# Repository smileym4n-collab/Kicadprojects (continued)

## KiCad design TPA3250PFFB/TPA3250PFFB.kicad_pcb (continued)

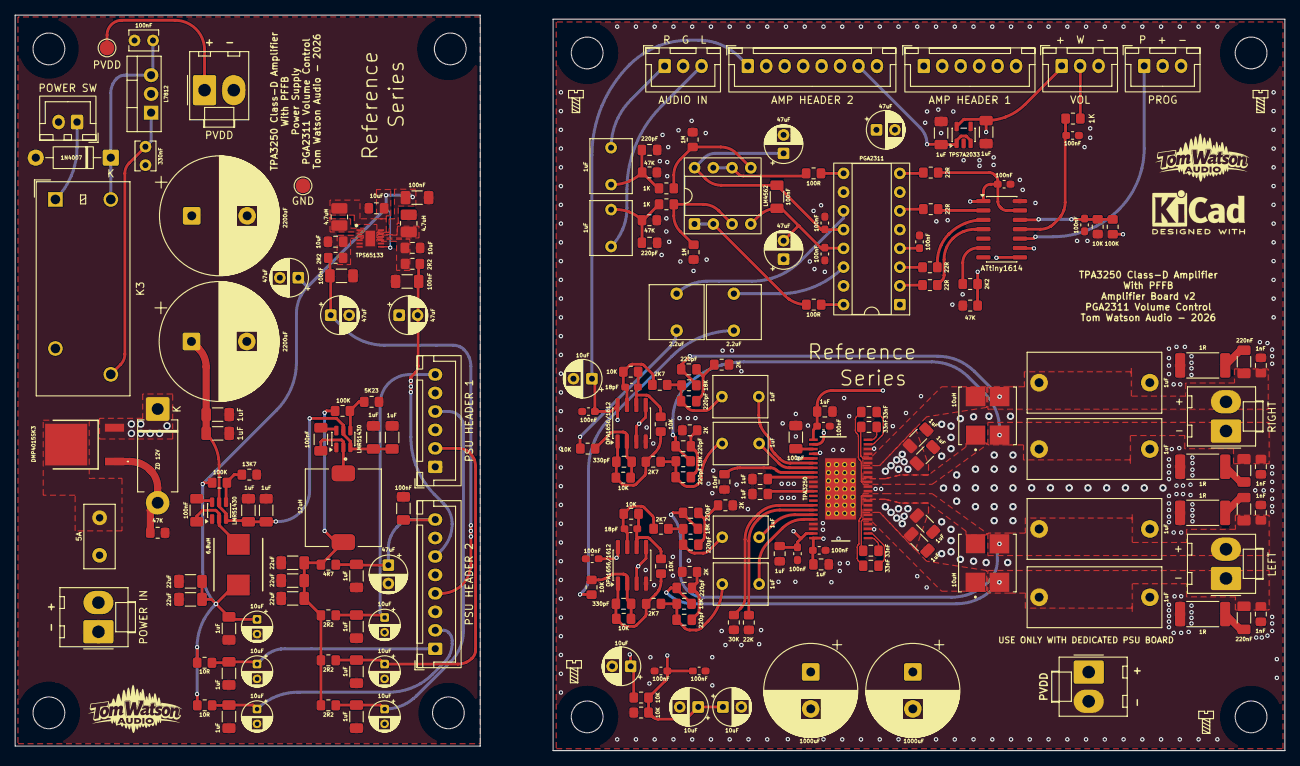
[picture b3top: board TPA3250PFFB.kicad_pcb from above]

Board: 4 copper layers, 172.0 x 99.6 mm, 218 parts (0 on the bottom side), 111 nets.

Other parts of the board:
J17: LEFT; Molex_KK-396_A-41791-0002_1x02_P3.96mm_Vertical
J18: RIGHT; Molex_KK-396_A-41791-0002_1x02_P3.96mm_Vertical

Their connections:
unnamed 66: J17.1; also elsewhere on the board
unnamed 67: J17.2; also elsewhere on the board
unnamed 68: J18.1; also elsewhere on the board
unnamed 69: J18.2; also elsewhere on the board

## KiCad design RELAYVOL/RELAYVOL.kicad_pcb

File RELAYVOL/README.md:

# RELAYVOL

Open [RELAYVOL.kicad_pro](RELAYVOL.kicad_pro) in KiCad 10 and open its schematic. Keep [RELAYVOL.kicad_sym](RELAYVOL.kicad_sym) and [sym-lib-table](sym-lib-table) beside the project. The project-local symbol divides each physical G6K relay into a left contact, a right contact and a coil. All three units share one footprint and reference designator.

The schematic is for a 5 V proof-of-concept attenuator. The 128 settled relay states were calculated and the schematic passed ERC and a pin-by-pin netlist audit. Hardware verification is pending.

- [Bill of materials](BOM.md)
- [Purchasing and stock](PURCHASING.md)
- [Resistor calculations, 128-state truth table and loading results](ATTENUATION.md)
- [KiCad 10.0.5 ERC report](ERC.rpt)

## Passive audio path

K1 to K7 switch 0.5, 1, 2, 4, 8, 16 and 32 dB pads, respectively. Each pole's COM is the stage output. With the coil off, COM touches NC and connects the shunt resistor from output to GNDA. The signal then passes through the series resistor. With the coil on, COM touches NO, connecting the stage input straight to the stage output and disconnecting the shunt. The same mechanism switches both channels. The only common audio connection is the return.

For a target loss A in dB, the voltage ratio is `k = 10^(−A/20)`. With downstream load Z = 10 kΩ, the ideal values are `Rseries = Z × (1 − k)` and `Rshunt = Z × k / (1 − k)`. These make each inserted stage look like 10 kΩ to the preceding stage. The fitted E96 pairs use one 0.1% thin-film resistor per position. The rounded values change the nominal step sizes.

For bench use, fit R29 and R30 as 10 kΩ and use a high-impedance instrument. For a known amplifier input resistance Ramp above 10 kΩ, choose a single resistor per channel using `Rterm = 1 / (1 / 10000 − 1 / Ramp)`, with resistances in ohms. With 47 kΩ inputs the exact value is 12.7027 kΩ. Use 12.7 kΩ, 0.1%, which gives an effective 9.9983 kΩ load. A 10 kΩ amplifier already provides the termination. An amplifier below 10 kΩ cannot reach a 10 kΩ effective load by adding a parallel resistor. Include any measuring instrument that remains connected in parallel when calculating the load.

Use a low-impedance, DC-free or AC-coupled source. At 2 Vrms into approximately 10 kΩ, total resistive dissipation is about 0.4 mW per channel. The 0.125 W thin-film parts have ample power margin. The highest calculated output resistance is about 3.30 kΩ at the bench load, so source impedance and cable or amplifier capacitance should be included when measuring frequency response. Omron's low-level contact reference condition is 10 µA at 10 mV DC. Some contacts can see less current at low signal levels and high attenuation. Check low-level continuity, noise, switching artefacts and channel separation on the prototype. [Omron G6K datasheet](https://components.omron.com/us-en/system/files/2026-05/datasheet_pdf/K106-E1.pdf)

## Assembly options and connectors

| Reference | Pin 1 | Pin 2 | Pin 3 |
|---|---|---|---|
| J1 power | Regulated +5 V | GND | — |
| J2 volume pot | +5 V, clockwise end | Wiper | GND, anticlockwise end |
| J3 UPDI | UPDI data | Target +5 V sense | GND |
| J4 left input | Left signal | GNDA | — |
| J5 right input | Right signal | GNDA | — |
| J6 left output | Left signal | GNDA | — |
| J7 right output | Right signal | GNDA | — |

| Build | Fit | JP1 and JP2 | Output at reset |
|---|---|---|---|
| Initial prototype | K1–K7 and their drivers | Bridge both | Ladder at maximum attenuation |
| With mute | K1–K8 and all drivers, including Q8, D8, R45 and R46 | Leave both open | J6/J7 signal pins grounded by K8 |

With K8 fitted, low on MUTE_CTRL grounds the outputs and high passes the ladder signal. R29/R30 are on the ladder side of K8, so grounding the outputs leaves the ladders terminated. The amplifier's parallel load joins them when K8 passes audio. If the jumpers are bridged with K8 fitted, K8 can ground the ladder outputs directly. Use one assembly option per board.

## MCU and volume input

U1 uses the user-approved wide SOIC-20 footprint, 7.5 × 12.8 mm nominal body and 1.27 mm lead pitch. Verify the physical package against the footprint before assembly. The stock record identified as SSOP-20 remains a separate package question. The following map uses the documented leaded ATtiny1616 pinout. [Microchip ATtiny1616 datasheet and package drawings](https://ww1.microchip.com/downloads/en/DeviceDoc/ATtiny1614-16-17-DataSheet-DS40002204A.pdf)

| Pin | Port | Function |
|---:|---|---|
| 1 | VDD | +5 V, C4 and C5 at the MCU |
| 2 | PA4 | RELAY_0_5DB, K1 |
| 3 | PA5 | RELAY_1DB, K2 |
| 4 | PA6 | RELAY_2DB, K3 |
| 5 | PA7 | RELAY_4DB, K4 |
| 6, 7 | PB5, PB4 | Unused |
| 8 | PB3 | MUTE_CTRL, optional K8 |
| 9 | PB2 | RELAY_32DB, K7 |
| 10 | PB1 | RELAY_16DB, K6 |
| 11 | PB0 | RELAY_8DB, K5 |
| 12–15 | PC0–PC3 | Unused |
| 16 | PA0/UPDI | J3 pin 1 |
| 17 | PA1/ADC0 AIN1 | VOL_ADC |
| 18, 19 | PA2, PA3 | Unused |
| 20 | GND | Digital return |

Use the internal oscillator and retain PA0 in UPDI mode. Use target-voltage sense on J3 pin 2 with the board powered from J1. R47 and C3 give a time constant of roughly 0.10–0.35 ms, including the wiper source resistance of a 10 kΩ pot. R48 pulls VOL_ADC low if the pot is disconnected. The ADC input is intended for the short internal wiring of a passive pot powered from J2. R47 limits transient injection and C3 filters the input. The header is a 0–5 V interface.

Use ADC0 with VDD as reference so slow supply changes track the pot voltage. Average ADC readings, add hysteresis around the 127 thresholds, and qualify state changes to limit chatter. The desired attenuation index is 127 at the anticlockwise end and 0 at the clockwise end. Gate pulldowns hold the relays off while the MCU pins are inputs. Initialise output latches low before enabling output direction. With K8 fitted, keep it off through startup and attenuation changes. Measure pickup, release and bounce with the flyback diodes fitted before setting the mute timing. Binary carries can change several contacts on one adjacent volume step.

## Coil supply and grounding

J1 takes regulated 5.0 V DC. Allow 0.5 A or more at the source and check the voltage at TP1 under an all-on relay load. The coil rating is 237 Ω and 21.1 mA typical at 23 °C. Seven coils draw approximately 148 mA and eight approximately 169 mA. At 5.25 V and −10% coil resistance, eight coils alone draw about 197 mA. The standard relay's must-operate limit is 4.0 V at 23 °C. C1 provides 220 µF bulk. C2 bypasses the incoming rail, C6 bypasses the local relay rail and C4/C5 decouple U1. [Omron G6K datasheet](https://components.omron.com/us-en/system/files/2026-05/datasheet_pdf/K106-E1.pdf)

Each 2N7002K is a low-side switch with a 330 Ω gate resistor and 100 kΩ gate pulldown. SOT-23 pins 1/2/3 are gate/source/drain. The stocked Multicomp Pro part is rated for 60 V VDS, ±20 V VGS and 300 mA continuous at 25 °C. Its published on-resistance table specifies 10 V drive. Its lower-gate-voltage data are typical, so verify pull-in and drain drop at 4.75 V supply and with warmed coils. For a same-pinout procurement option, Diodes Inc. specifies a maximum of 3 Ω at 4.5 V gate drive, equivalent to about 63 mV and 1.3 mW at 21.1 mA using that limit. D1–D8 use SOD-123 pin 1 cathode to +5 V and pin 2 anode to drain. Initial flyback current is approximately the preceding coil current. [Stock MOSFET datasheet](https://www.farnell.com/datasheets/4495380.pdf) · [Diodes Inc. 2N7002K](https://www.diodes.com/assets/datasheets/ds30896.pdf) · [1N4148W SOD-123 datasheet](https://www.vishay.com/docs/86356/1n4148w.pdf)

For layout, return the drivers and supply bypass currents to J1 ground without sharing their route with audio return currents. Join GNDA to GND at NT1 near the supply return. Check any additional connection between these returns through the enclosure, source, amplifier or programmer. TP1 and TP2 expose +5 V and GND.

## Pin and footprint verification

| Part | Verified assignment |
|---|---|
| K1–K8 | Pin 1 coil positive, 8 coil negative. Left COM/NC/NO 3/2/4. Right COM/NC/NO 6/7/5. Standard G6K-2P hole pattern has 5.08 mm row separation, 2.54 mm pitch along each row and eight 0.85 mm holes. |
| Stock G6K-2P-Y | Same electrical pin functions. Its intermediate pins lie at 3.2 and 5.4 mm from the end-pin datum and its end-pin spacing is 7.6 mm. This differs from the standard G6K-2P pattern. |
| U1 | KiCad ATtiny1616-S symbol and matching wide SOIC-20 footprint, pad 1 VDD and pad 20 GND. No exposed pad. |
| Q1–Q8 / D1–D8 | KiCad 2N7002K SOT-23 and 1N4148W SOD-123 symbols and matching footprints. |
| C1 | Rubycon ZLH, 8 mm body diameter, 3.50 mm pitch, pin 1 positive. |
| J1 / J2–J7 | JST XH 2.50 mm power input, and single-row 2.54 mm through-hole headers for control and audio. |
| Resistors and ceramics | 1608 and 2012 metric footprints, as itemised in the BOM. |

Sources for the mechanical assignments include [Omron G6K datasheet](https://components.omron.com/us-en/system/files/2026-05/datasheet_pdf/K106-E1.pdf), [JST XH series drawing](https://order.jst-mfg.com/InternetShop/app/pdf_show.php?kbn=1&key=eXH.pdf), [Rubycon C1 part data](https://www.digikey.com/en/products/detail/rubycon/35ZLH220MEFC8X11-5/3563385) and [Samsung C5 component data](https://product.samsungsem.com/mlcc/CL21A475KAQNNN.do).

## Validation

KiCad 10.0.5 reports 0 errors and 0 warnings with the project defaults. An independent comparison of the exported netlist verified the exact node membership of 70 nets, including the eight intentionally unused MCU pins. The audit matched all 256 physical pins to pads across 91 footprints and checked the five DNP references. The analogue model uses the values exported from this schematic. The PCB and physical operating behaviour remain to be verified on a prototype.

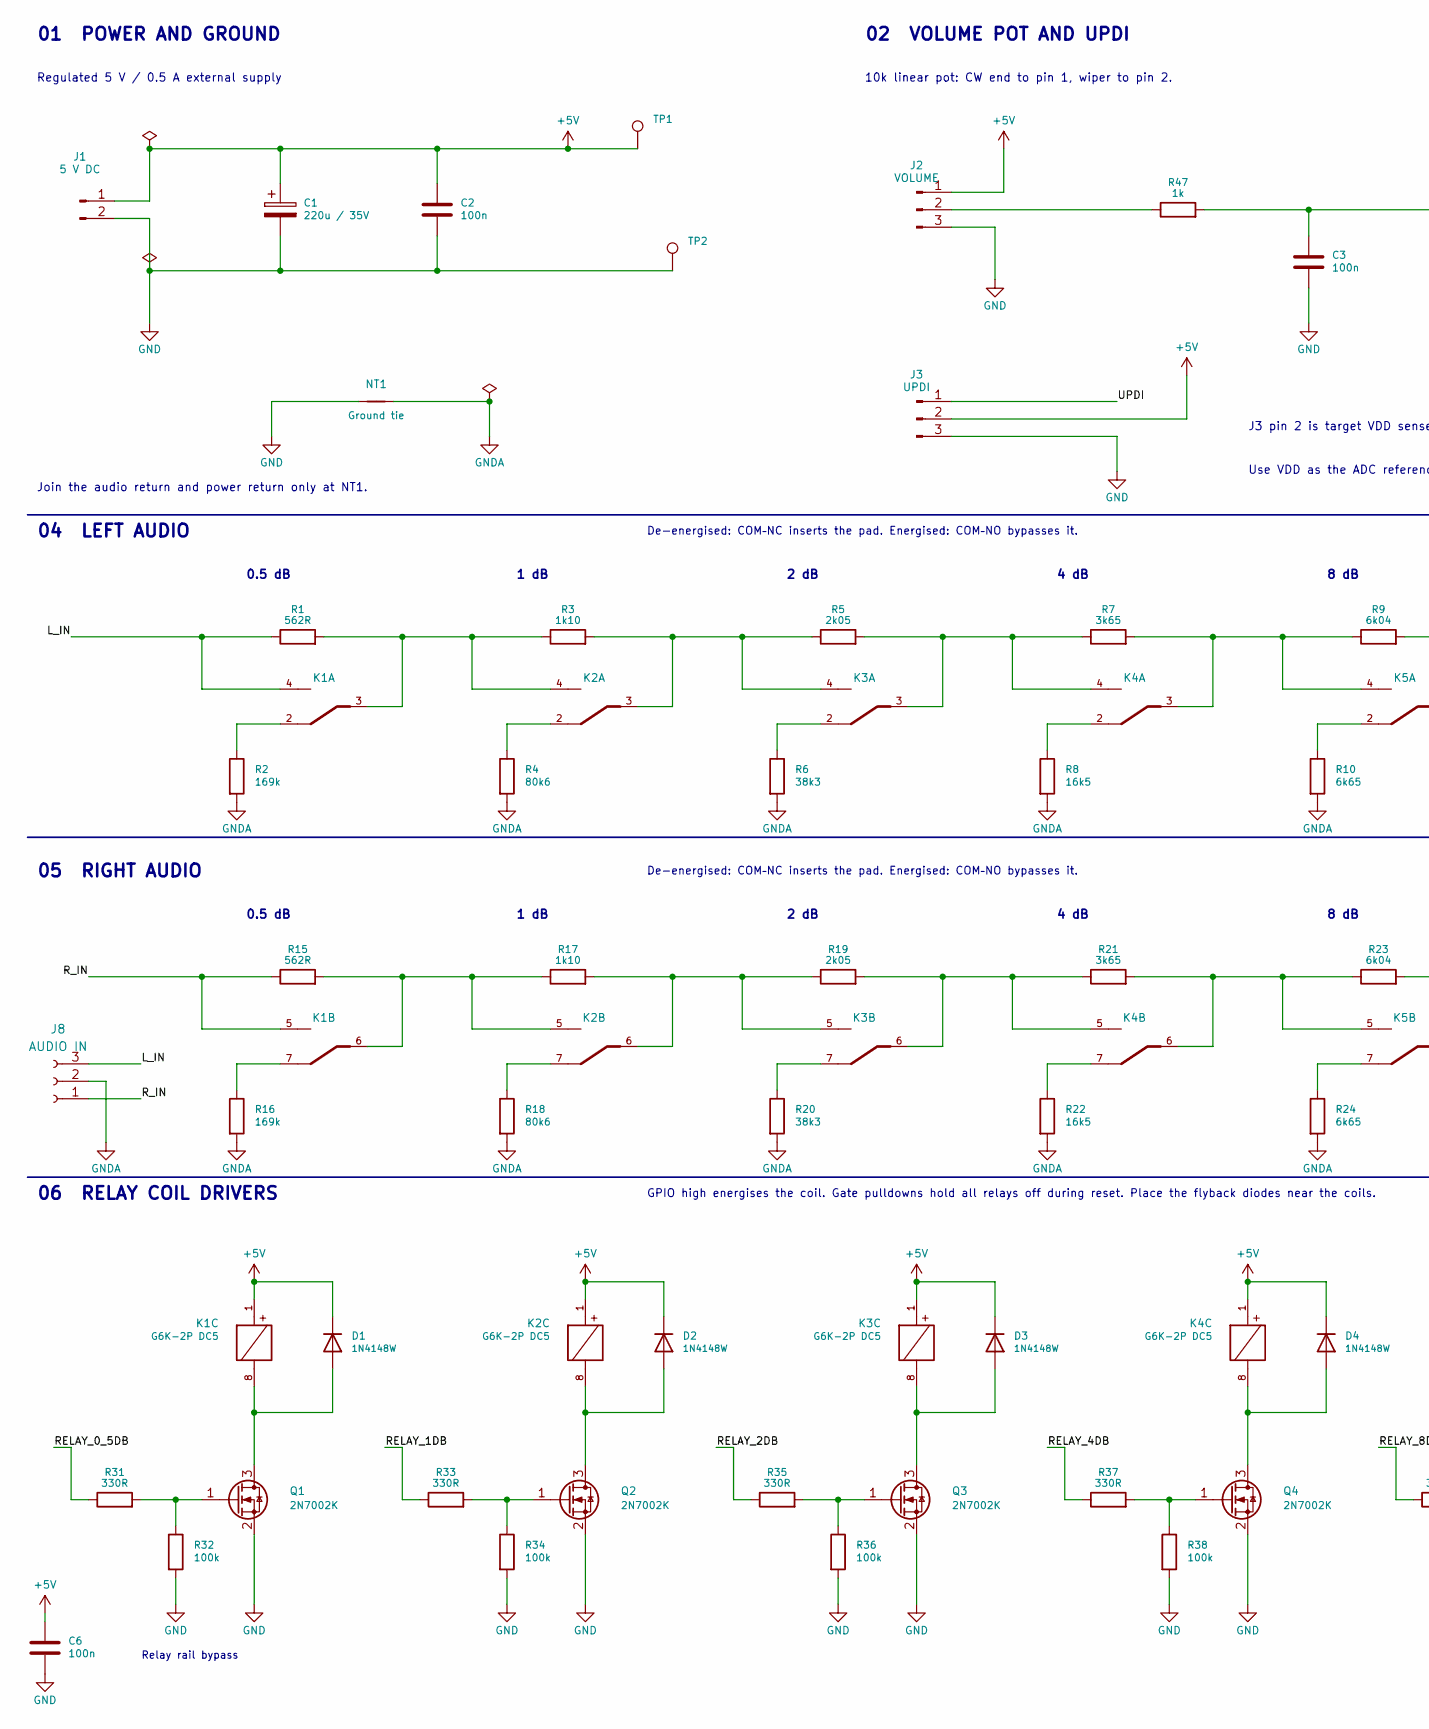
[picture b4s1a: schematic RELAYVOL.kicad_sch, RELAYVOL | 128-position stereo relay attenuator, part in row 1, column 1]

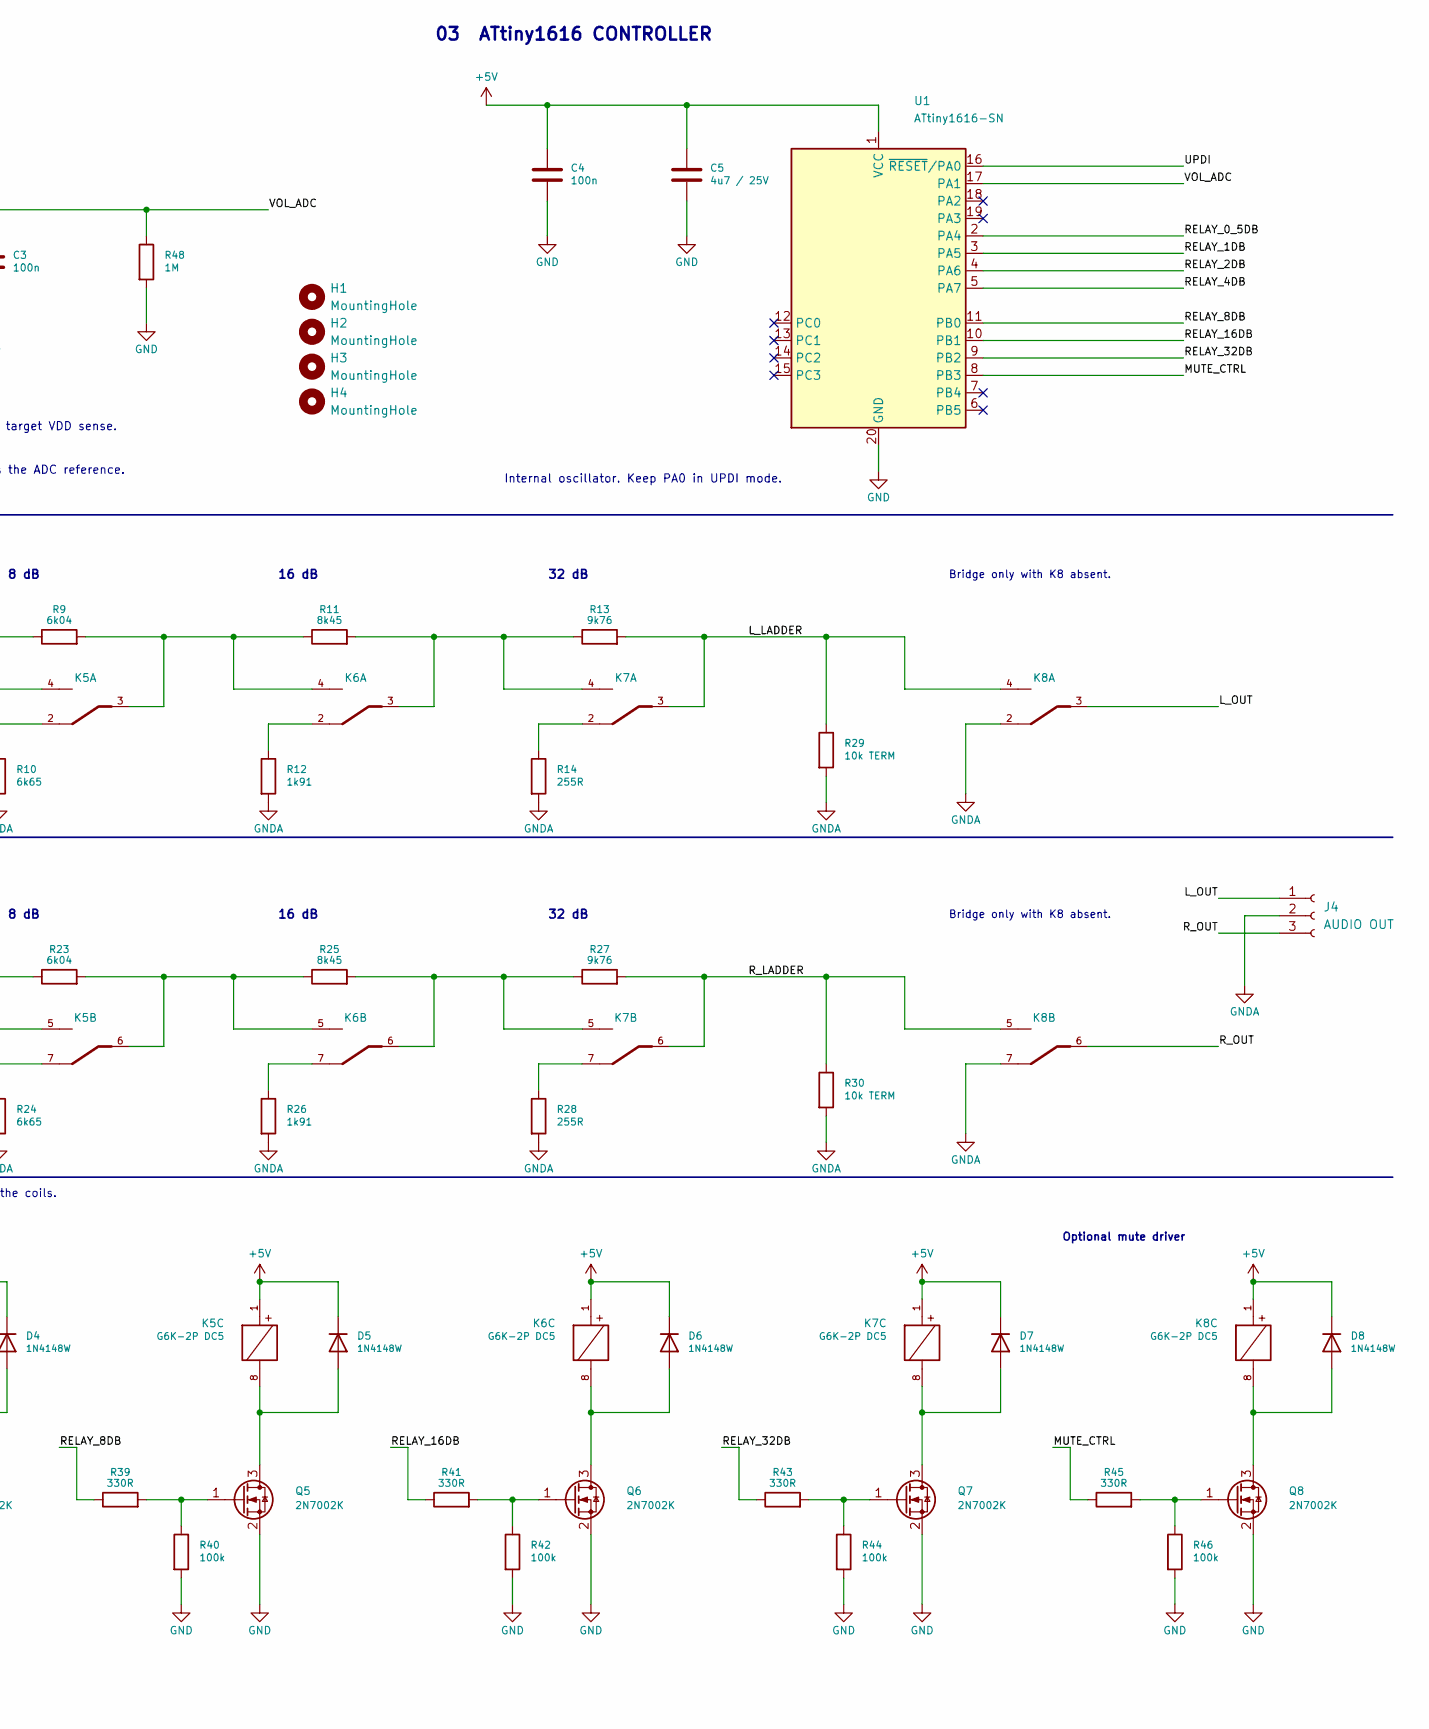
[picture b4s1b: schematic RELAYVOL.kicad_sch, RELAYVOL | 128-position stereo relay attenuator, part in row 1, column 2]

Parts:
C1: 220u / 35V; CP_Radial_D8.0mm_P3.50mm; MPN 35ZLH220MEFC8X11.5
C2, C3, C4, C6: 100n; C_0603_1608Metric; MPN MC0603B104K500CT
C5: 4u7 / 25V; C_0805_2012Metric; MPN CL21A475KAQNNNE
D1, D2, D3, D4, D5, D6, D7, D8: 1N4148W; D_SOD-123; MPN 1N4148W
H1, H2, H3, H4: MountingHole; MountingHole_3.2mm_M3
J1: 5 V DC; JST_XH_B2B-XH-A_1x02_P2.50mm_Vertical; MPN B2B-XH-A(LF)(SN)
J2: VOLUME; PinHeader_1x03_P2.54mm_Vertical
J3: UPDI; PinHeader_1x03_P2.54mm_Vertical
J4: AUDIO OUT; JST_XH_B3B-XH-A_1x03_P2.50mm_Vertical
J8: AUDIO IN; JST_XH_B3B-XH-A_1x03_P2.50mm_Vertical
K1, K2, K3, K4, K5, K6, K7, K8: G6K-2P DC5; Relay_DPDT_Omron_G6K-2P; MPN G6K-2P DC5
NT1: Ground tie; NetTie-2_SMD_Pad2.0mm
Q1, Q2, Q3, Q4, Q5, Q6, Q7, Q8: 2N7002K; SOT-23; MPN 2N7002K
R1, R15: 562R; R_0805_2012Metric; MPN ERA-6AEB5620V
R2, R16: 169k; R_0805_2012Metric; MPN RT0805BRD07169KL
R3, R17: 1k10; R_0805_2012Metric; MPN RT0805BRD071K1L
R4, R18: 80k6; R_0805_2012Metric; MPN ERA-6AEB8062V
R5, R19: 2k05; R_0805_2012Metric; MPN RT0805BRD072K05L
R6, R20: 38k3; R_0805_2012Metric; MPN ERA-6AEB3832V
R7, R21: 3k65; R_0805_2012Metric; MPN RG2012P-3651-B-T5
R8, R22: 16k5; R_0805_2012Metric; MPN RG2012P-1652-B-T5
R9, R23: 6k04; R_0805_2012Metric; MPN ERA-6AEB6041V
R10, R24: 6k65; R_0805_2012Metric; MPN ERA-6AEB6651V
R11, R25: 8k45; R_0805_2012Metric; MPN ERA-6AEB8451V
R12, R26: 1k91; R_0805_2012Metric; MPN RT0805BRD071K91L
R13, R27: 9k76; R_0805_2012Metric; MPN ERA-6AEB9761V
R14, R28: 255R; R_0805_2012Metric; MPN RG2012P-2550-B-T5
R29, R30: 10k TERM; R_0805_2012Metric; MPN RG2012P-103-B-T5
R31, R33, R35, R37, R39, R41, R43, R45: 330R; R_0603_1608Metric; MPN RC0603FR-10330RL
R32, R34, R36, R38, R40, R42, R44, R46: 100k; R_0805_2012Metric; MPN RT0805DRE07100KL
R47: 1k; R_0603_1608Metric; MPN RC0603FR-101KL
R48: 1M; R_0603_1608Metric; MPN RC0603FR-101ML
TP1: 5 V; TestPoint_Pad_D2.0mm
TP2: Digital GND; TestPoint_Pad_D2.0mm
U1: ATtiny1616-SN; SOIC-20W_7.5x12.8mm_P1.27mm; MPN ATTINY1616-SN

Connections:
+5V: C1.1, C2.1, C4.1, C5.1, C6.1, D1.1 (K), D2.1 (K), D3.1 (K), D4.1 (K), D5.1 (K), D6.1 (K), D7.1 (K), D8.1 (K), J1.1, J2.1, J3.2, K1.1 (COIL+), K2.1 (COIL+), K3.1 (COIL+), K4.1 (COIL+), K5.1 (COIL+), K6.1 (COIL+), K7.1 (COIL+), K8.1 (COIL+), TP1.1 (1_1), U1.1 (VCC)
/L_IN: J8.3, K1.4 (NO), R1.1
/L_LADDER: K7.3 (COM), K8.4 (NO), R13.2, R29.1
/L_OUT: J4.1, K8.3 (COM)
/MUTE_CTRL: R45.1, U1.8 (PB3)
/RELAY_0_5DB: R31.1, U1.2 (PA4)
/RELAY_1DB: R33.1, U1.3 (PA5)
/RELAY_2DB: R35.1, U1.4 (PA6)
/RELAY_4DB: R37.1, U1.5 (PA7)
/RELAY_8DB: R39.1, U1.11 (PB0)
/RELAY_16DB: R41.1, U1.10 (PB1)
/RELAY_32DB: R43.1, U1.9 (PB2)
/R_IN: J8.1, K1.5 (NO), R15.1
/R_LADDER: K7.6 (COM), K8.5 (NO), R27.2, R30.1
/R_OUT: J4.3, K8.6 (COM)
/UPDI: J3.1, U1.16 (~RESET/PA0)
/VOL_ADC: C3.1, R47.2, R48.1, U1.17 (PA1)
GND: C1.2, C2.2, C3.2, C4.2, C5.2, C6.2, J1.2, J2.3, J3.3, NT1.1, Q1.2 (S), Q2.2 (S), Q3.2 (S), Q4.2 (S), Q5.2 (S), Q6.2 (S), Q7.2 (S), Q8.2 (S), R32.2, R34.2, R36.2, R38.2, R40.2, R42.2, R44.2, R46.2, R48.2, TP2.1 (1_1), U1.20 (GND)
GNDA: J4.2, J8.2, K8.2 (NC), K8.7 (NC), NT1.2, R2.2, R4.2, R6.2, R8.2, R10.2, R12.2, R14.2, R16.2, R18.2, R20.2, R22.2, R24.2, R26.2, R28.2, R29.2, R30.2
unnamed: D1.2 (A), K1.8 (COIL-), Q1.3 (D)
unnamed: D2.2 (A), K2.8 (COIL-), Q2.3 (D)
unnamed: D3.2 (A), K3.8 (COIL-), Q3.3 (D)
unnamed: D4.2 (A), K4.8 (COIL-), Q4.3 (D)
unnamed: D5.2 (A), K5.8 (COIL-), Q5.3 (D)
unnamed: D6.2 (A), K6.8 (COIL-), Q6.3 (D)
unnamed: D7.2 (A), K7.8 (COIL-), Q7.3 (D)
unnamed: D8.2 (A), K8.8 (COIL-), Q8.3 (D)
unnamed: J2.2, R47.1
unnamed: K1.3 (COM), K2.4 (NO), R1.2, R3.1
unnamed: K1.2 (NC), R2.1
unnamed: K1.6 (COM), K2.5 (NO), R15.2, R17.1
unnamed: K1.7 (NC), R16.1
unnamed: K2.3 (COM), K3.4 (NO), R3.2, R5.1
unnamed: K2.2 (NC), R4.1
unnamed: K2.6 (COM), K3.5 (NO), R17.2, R19.1
unnamed: K2.7 (NC), R18.1
unnamed: K3.3 (COM), K4.4 (NO), R5.2, R7.1
unnamed: K3.2 (NC), R6.1
unnamed: K3.6 (COM), K4.5 (NO), R19.2, R21.1
unnamed: K3.7 (NC), R20.1
unnamed: K4.3 (COM), K5.4 (NO), R7.2, R9.1
unnamed: K4.2 (NC), R8.1
unnamed: K4.6 (COM), K5.5 (NO), R21.2, R23.1
unnamed: K4.7 (NC), R22.1
unnamed: K5.3 (COM), K6.4 (NO), R9.2, R11.1
unnamed: K5.2 (NC), R10.1
unnamed: K5.6 (COM), K6.5 (NO), R23.2, R25.1
unnamed: K5.7 (NC), R24.1
unnamed: K6.3 (COM), K7.4 (NO), R11.2, R13.1
unnamed: K6.2 (NC), R12.1
unnamed: K6.6 (COM), K7.5 (NO), R25.2, R27.1
unnamed: K6.7 (NC), R26.1
unnamed: K7.2 (NC), R14.1
unnamed: K7.7 (NC), R28.1
unnamed: Q1.1 (G), R31.2, R32.1
unnamed: Q2.1 (G), R33.2, R34.1
unnamed: Q3.1 (G), R35.2, R36.1
unnamed: Q4.1 (G), R37.2, R38.1
unnamed: Q5.1 (G), R39.2, R40.1
unnamed: Q6.1 (G), R41.2, R42.1
unnamed: Q7.1 (G), R43.2, R44.1
unnamed: Q8.1 (G), R45.2, R46.1

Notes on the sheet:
16 dB
J3 pin 2 is target VDD sense.
2 dB
03 ATtiny1616 CONTROLLER
06 RELAY COIL DRIVERS
0.5 dB
05 RIGHT AUDIO
1 dB
Bridge only with K8 absent.
Use VDD as the ADC reference.
32 dB
01 POWER AND GROUND
04 LEFT AUDIO
8 dB
GPIO high energises the coil. Gate pulldowns hold all relays off during reset. Place the flyback diodes near the coils.
4 dB
Internal oscillator. Keep PA0 in UPDI mode.
Regulated 5 V / 0.5 A external supply
De-energised: COM–NC inserts the pad. Energised: COM–NO bypasses it.
10k linear pot: CW end to pin 1, wiper to pin 2.
Join the audio return and power return only at NT1.
Relay rail bypass
02 VOLUME POT AND UPDI
Optional mute driver

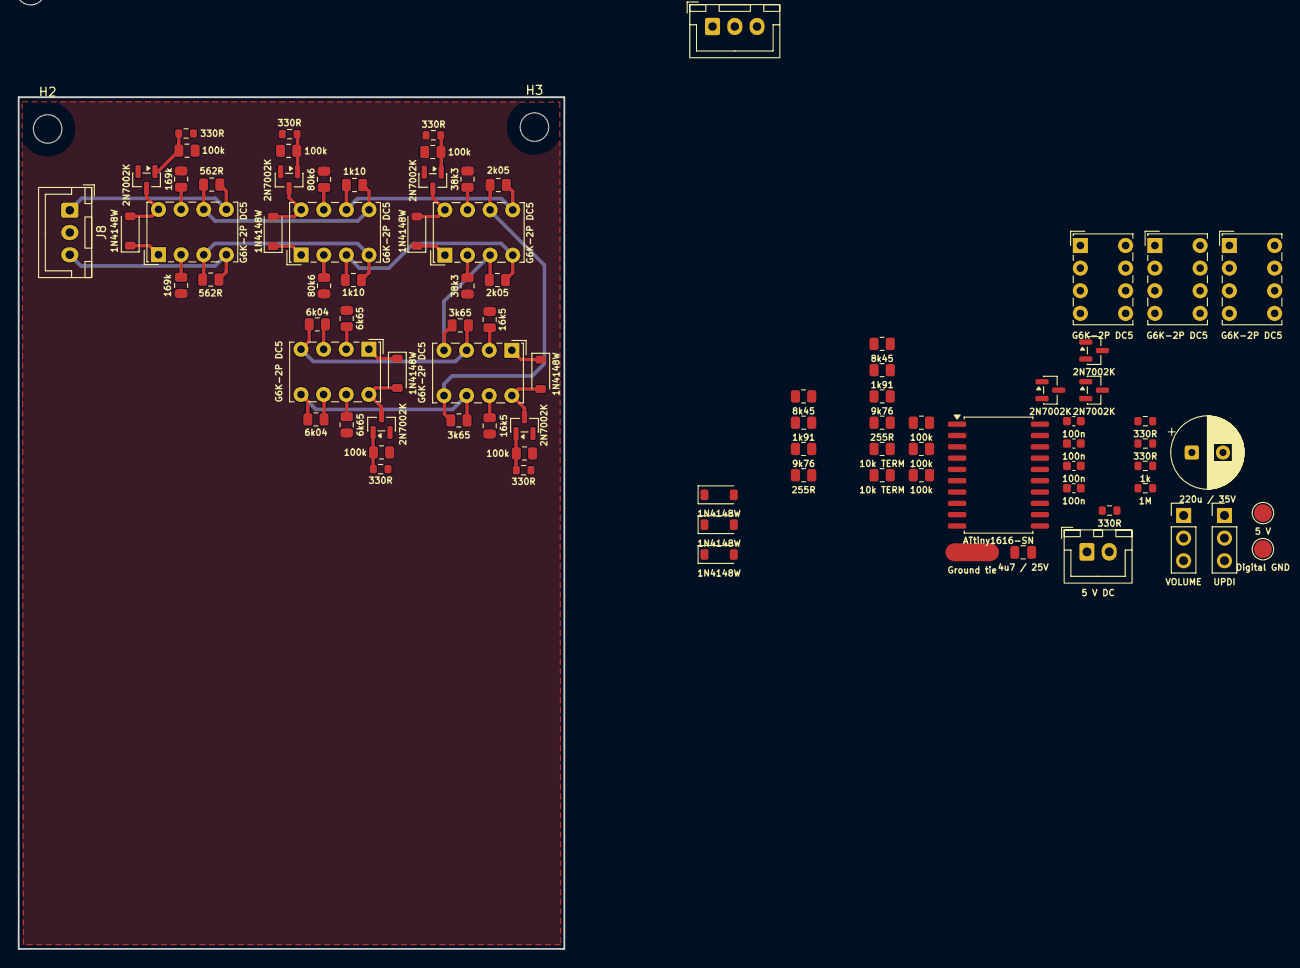
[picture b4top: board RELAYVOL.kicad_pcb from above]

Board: 2 copper layers, 61.3 x 95.6 mm, 91 parts (0 on the bottom side), 62 nets.

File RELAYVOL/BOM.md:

# RELAYVOL bill of materials

Quantities are for one stereo board. The default build leaves K8 and its driver unpopulated. Close JP1 and JP2 for that build.

| References | Qty | Build | Value | MPN or specification | KiCad footprint |
|---|---:|---|---|---|---|
| C1 | 1 | Fit | 220u / 35V | 35ZLH220MEFC8X11.5 · Rubycon ZLH radial electrolytic | `Capacitor_THT:CP_Radial_D8.0mm_P3.50mm` |
| C2, C3, C4, C6 | 4 | Fit | 100n | MC0603B104K500CT · X7R, 50 V, 1608 metric | `Capacitor_SMD:C_0603_1608Metric` |
| C5 | 1 | Fit | 4u7 / 25V | CL21A475KAQNNNE · X5R, 25 V, 2012 metric | `Capacitor_SMD:C_0805_2012Metric` |
| D1, D2, D3, D4, D5, D6, D7 | 7 | Fit | 1N4148W | 1N4148W · Fast switching diode, SOD-123 | `Diode_SMD:D_SOD-123` |
| D8 | 1 | Optional | 1N4148W | 1N4148W · Fast switching diode, SOD-123 | `Diode_SMD:D_SOD-123` |
| J1 | 1 | Fit | 5 V DC | B2B-XH-A(LF)(SN) · Through-hole header | `Connector_JST:JST_XH_B2B-XH-A_1x02_P2.50mm_Vertical` |
| J2 | 1 | Fit | VOLUME | Through-hole header | `Connector_PinHeader_2.54mm:PinHeader_1x03_P2.54mm_Vertical` |
| J3 | 1 | Fit | UPDI | Through-hole header | `Connector_PinHeader_2.54mm:PinHeader_1x03_P2.54mm_Vertical` |
| J4 | 1 | Fit | LEFT IN | Through-hole header | `Connector_PinHeader_2.54mm:PinHeader_1x02_P2.54mm_Vertical` |
| J5 | 1 | Fit | RIGHT IN | Through-hole header | `Connector_PinHeader_2.54mm:PinHeader_1x02_P2.54mm_Vertical` |
| J6 | 1 | Fit | LEFT OUT | Through-hole header | `Connector_PinHeader_2.54mm:PinHeader_1x02_P2.54mm_Vertical` |
| J7 | 1 | Fit | RIGHT OUT | Through-hole header | `Connector_PinHeader_2.54mm:PinHeader_1x02_P2.54mm_Vertical` |
| K1, K2, K3, K4, K5, K6, K7 | 7 | Fit | G6K-2P DC5 | G6K-2P DC5 · Omron DPDT non-latching, through-hole | `Relay_THT:Relay_DPDT_Omron_G6K-2P` |
| K8 | 1 | Optional | G6K-2P DC5 | G6K-2P DC5 · Omron DPDT non-latching, through-hole | `Relay_THT:Relay_DPDT_Omron_G6K-2P` |
| Q1, Q2, Q3, Q4, Q5, Q6, Q7 | 7 | Fit | 2N7002K | 2N7002K · G/S/D = 1/2/3, SOT-23 | `Package_TO_SOT_SMD:SOT-23` |
| Q8 | 1 | Optional | 2N7002K | 2N7002K · G/S/D = 1/2/3, SOT-23 | `Package_TO_SOT_SMD:SOT-23` |
| R1, R15 | 2 | Fit | 562R | ERA-6AEB5620V · 0.1% thin-film, 2012 metric | `Resistor_SMD:R_0805_2012Metric` |
| R2, R16 | 2 | Fit | 169k | RT0805BRD07169KL · 0.1% thin-film, 2012 metric | `Resistor_SMD:R_0805_2012Metric` |
| R3, R17 | 2 | Fit | 1k10 | RT0805BRD071K1L · 0.1% thin-film, 2012 metric | `Resistor_SMD:R_0805_2012Metric` |
| R4, R18 | 2 | Fit | 80k6 | ERA-6AEB8062V · 0.1% thin-film, 2012 metric | `Resistor_SMD:R_0805_2012Metric` |
| R5, R19 | 2 | Fit | 2k05 | RT0805BRD072K05L · 0.1% thin-film, 2012 metric | `Resistor_SMD:R_0805_2012Metric` |
| R6, R20 | 2 | Fit | 38k3 | ERA-6AEB3832V · 0.1% thin-film, 2012 metric | `Resistor_SMD:R_0805_2012Metric` |
| R7, R21 | 2 | Fit | 3k65 | RG2012P-3651-B-T5 · 0.1% thin-film, 2012 metric | `Resistor_SMD:R_0805_2012Metric` |
| R8, R22 | 2 | Fit | 16k5 | RG2012P-1652-B-T5 · 0.1% thin-film, 2012 metric | `Resistor_SMD:R_0805_2012Metric` |
| R9, R23 | 2 | Fit | 6k04 | ERA-6AEB6041V · 0.1% thin-film, 2012 metric | `Resistor_SMD:R_0805_2012Metric` |
| R10, R24 | 2 | Fit | 6k65 | ERA-6AEB6651V · 0.1% thin-film, 2012 metric | `Resistor_SMD:R_0805_2012Metric` |
| R11, R25 | 2 | Fit | 8k45 | ERA-6AEB8451V · 0.1% thin-film, 2012 metric | `Resistor_SMD:R_0805_2012Metric` |
| R12, R26 | 2 | Fit | 1k91 | RT0805BRD071K91L · 0.1% thin-film, 2012 metric | `Resistor_SMD:R_0805_2012Metric` |
| R13, R27 | 2 | Fit | 9k76 | ERA-6AEB9761V · 0.1% thin-film, 2012 metric | `Resistor_SMD:R_0805_2012Metric` |
| R14, R28 | 2 | Fit | 255R | RG2012P-2550-B-T5 · 0.1% thin-film, 2012 metric | `Resistor_SMD:R_0805_2012Metric` |
| R29, R30 | 2 | Fit | 10k TERM | RG2012P-103-B-T5 · 0.1% thin-film, 2012 metric; replace to suit amplifier input | `Resistor_SMD:R_0805_2012Metric` |
| R31, R33, R35, R37, R39, R41, R43 | 7 | Fit | 330R | RC0603FR-10330RL · 1%, 1608 metric | `Resistor_SMD:R_0603_1608Metric` |
| R32, R34, R36, R38, R40, R42, R44 | 7 | Fit | 100k | RT0805DRE07100KL · 0.5%, 2012 metric | `Resistor_SMD:R_0805_2012Metric` |
| R45 | 1 | Optional | 330R | RC0603FR-10330RL · 1%, 1608 metric | `Resistor_SMD:R_0603_1608Metric` |
| R46 | 1 | Optional | 100k | RT0805DRE07100KL · 0.5%, 2012 metric | `Resistor_SMD:R_0805_2012Metric` |
| R47 | 1 | Fit | 1k | RC0603FR-101KL · 1%, 1608 metric | `Resistor_SMD:R_0603_1608Metric` |
| R48 | 1 | Fit | 1M | RC0603FR-101ML · 1%, 1608 metric, unplugged-wiper pulldown | `Resistor_SMD:R_0603_1608Metric` |
| U1 | 1 | Fit | ATtiny1616-SN | ATTINY1616-SN · Wide SOIC-20, approved footprint | `Package_SO:SOIC-20W_7.5x12.8mm_P1.27mm` |

## Copper features

| References | Qty | Function | KiCad footprint |
|---|---:|---|---|
| JP1, JP2 | 2 | Open solder jumpers. Bridge both only with K8 absent. | `Jumper:SolderJumper-2_P1.3mm_Open_RoundedPad1.0x1.5mm` |
| NT1 | 1 | Copper net tie between GND and GNDA | `NetTie:NetTie-2_SMD_Pad2.0mm` |
| TP1, TP2 | 2 | +5 V and GND probe pads | `TestPoint:TestPoint_Pad_D2.0mm` |

## Off-board parts

| Qty | Item | Specification |
|---:|---|---|
| 1 | Volume pot | 10 kΩ linear, single-gang, e.g. Bourns PTV09A-4020F-B103 |
| 1 | Regulated power source | 5.0 V DC, 0.5 A or greater. Board-side J1 polarity is 1 +5 V, 2 GND. |
| 1 | J1 mating housing | JST XHP-2 with two SXH-001T-P0.6 terminals for suitable wire, or a matching pre-crimped lead |
| 2 | Mating 1×3 connectors | 2.54 mm sockets or leads for J2 and J3, according to the pot and programmer harnesses |
| 4 | Mating 1×2 connectors | 2.54 mm sockets or leads for the four audio headers |

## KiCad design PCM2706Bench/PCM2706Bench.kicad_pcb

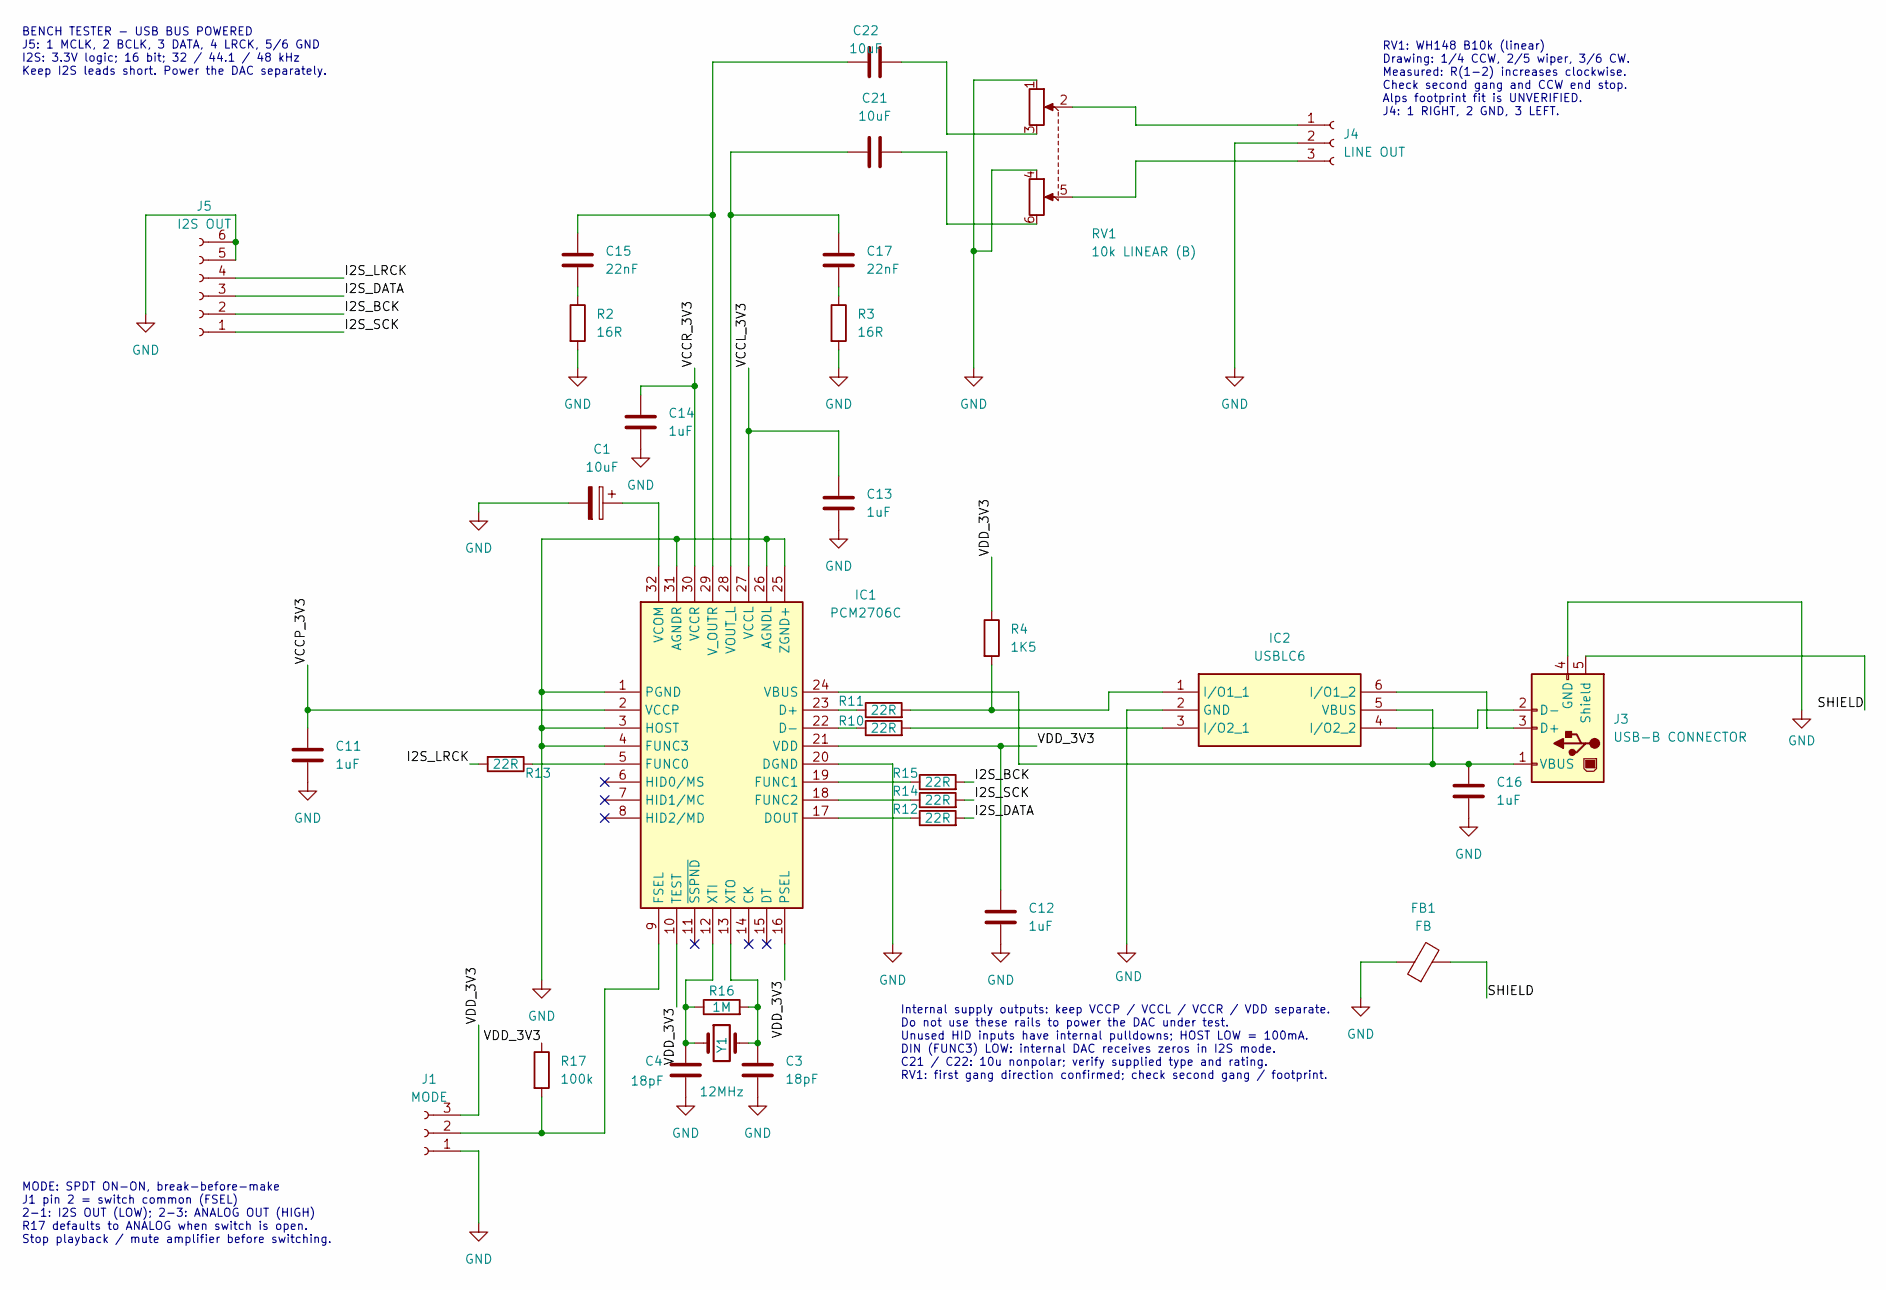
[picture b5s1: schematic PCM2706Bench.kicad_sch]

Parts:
C1: 10uF; CP_Radial_D5.0mm_P2.00mm
C3, C4: 18pF; C_0603_1608Metric_Pad1.08x0.95mm_HandSolder
C11, C12, C13, C14, C16: 1uF; C_0805_2012Metric_Pad1.18x1.45mm_HandSolder
C15, C17: 22nF; C_Rect_L7.2mm_W2.5mm_P5.00mm
C21, C22: 10uF; C_Radial_D8.0mm_H11.5mm_P3.50mm
FB1: FB; L_1206_3216Metric_Pad1.22x1.90mm_HandSolder
IC1: PCM2706C; Mouser Part Number 595-PCM2706CPJTR
IC2: USBLC6; SOT-23-6_Handsoldering; Mouser Part Number 511-USBLC6-2SC6
J1: MODE; PinHeader_1x03_P2.54mm_Vertical
J3: USB-B CONNECTOR; USBC
J4: LINE OUT; JST_XH_B3B-XH-A_1x03_P2.50mm_Vertical
J5: I2S OUT; JST_XH_B6B-XH-A_1x06_P2.50mm_Vertical; Manufacturer_Part_Number MC34635
R2, R3: 16R; R_0805_2012Metric_Pad1.20x1.40mm_HandSolder
R4: 1K5; R_0603_1608Metric_Pad0.98x0.95mm_HandSolder
R10, R11, R12, R13, R14, R15: 22R; R_0603_1608Metric_Pad0.98x0.95mm_HandSolder
R16: 1M; R_0603_1608Metric_Pad0.98x0.95mm_HandSolder
R17: 100k; R_0805_2012Metric_Pad1.20x1.40mm_HandSolder
RV1: 10k LINEAR (B); Potentiometer_Alps_RK163_Dual_Horizontal
Y1: 12MHz; Crystal_HC49-U_Vertical

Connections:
/I2S_BCK: J5.2, R15.2
/I2S_DATA: J5.3, R12.2
/I2S_LRCK: J5.4, R13.2
/I2S_SCK: J5.1, R14.2
/SHIELD: FB1.2, J3.5 (Shield)
/VCCL_3V3: C13.1, IC1.27 (VCCL)
/VCCP_3V3: C11.1, IC1.2 (VCCP)
/VCCR_3V3: C14.1, IC1.30 (VCCR)
/VDD_3V3: C12.1, IC1.10 (TEST), IC1.16 (PSEL), IC1.21 (VDD), J1.3, R4.1, R17.1
GND: C1.2, C3.2, C4.2, C11.2, C12.2, C13.2, C14.2, C16.2, FB1.1, IC1.1 (PGND), IC1.3 (HOST), IC1.4 (FUNC3), IC1.20 (DGND), IC1.25 (ZGND+), IC1.26 (AGNDL), IC1.31 (AGNDR), IC2.2 (GND), J1.1, J3.4 (GND), J4.2, J5.5, J5.6, R2.2, R3.2, RV1.1, RV1.4
unnamed: C15.2, R2.1
unnamed: C17.2, R3.1
unnamed: C21.2, RV1.6
unnamed: C22.2, RV1.3
unnamed: IC1.23 (D+), R11.1
unnamed: IC1.22 (D-), R10.1
unnamed: IC1.17 (DOUT), R12.1
unnamed: IC1.9 (FSEL), J1.2, R17.2
unnamed: IC1.5 (FUNC0), R13.1
unnamed: IC1.19 (FUNC1), R15.1
unnamed: IC1.18 (FUNC2), R14.1
unnamed: C16.1, IC1.24 (VBUS), IC2.5 (VBUS), J3.1 (VBUS)
unnamed: C1.1, IC1.32 (VCOM)
unnamed: C17.1, C21.1, IC1.28 (VOUT_L)
unnamed: C15.1, C22.1, IC1.29 (V_OUTR)
unnamed: C4.1, IC1.12 (XTI), R16.1, Y1.1
unnamed: C3.1, IC1.13 (XTO), R16.2, Y1.2
unnamed: IC2.1 (I/O1_1), R4.2, R11.2
unnamed: IC2.6 (I/O1_2), J3.3 (D+)
unnamed: IC2.3 (I/O2_1), R10.2
unnamed: IC2.4 (I/O2_2), J3.2 (D-)
unnamed: J4.1, RV1.2
unnamed: J4.3, RV1.5

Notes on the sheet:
BENCH TESTER - USB BUS POWERED J5: 1 MCLK, 2 BCLK, 3 DATA, 4 LRCK, 5/6 GND I2S: 3.3V logic; 16 bit; 32 / 44.1 / 48 kHz Keep I2S leads short. Power the DAC separately.
Internal supply outputs: keep VCCP / VCCL / VCCR / VDD separate. Do not use these rails to power the DAC under test. Unused HID inputs have internal pulldowns; HOST LOW = 100mA. DIN (FUNC3) LOW: internal DAC receives zeros in I2S mode. C21 / C22: 10u nonpolar; verify supplied type and rating. RV1: 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
MODE: SPDT ON-ON, break-before-make J1 pin 2 = switch common (FSEL) 2-1: I2S OUT (LOW); 2-3: ANALOG OUT (HIGH) R17 defaults to ANALOG when switch is open. Stop playback / mute amplifier before switching.
RV1: WH148 B10k (linear) Drawing: 1/4 CCW, 2/5 wiper, 3/6 CW. Measured: R(1-2) increases clockwise. Check second gang and CCW end stop. Alps footprint fit is UNVERIFIED. J4: 1 RIGHT, 2 GND, 3 LEFT.

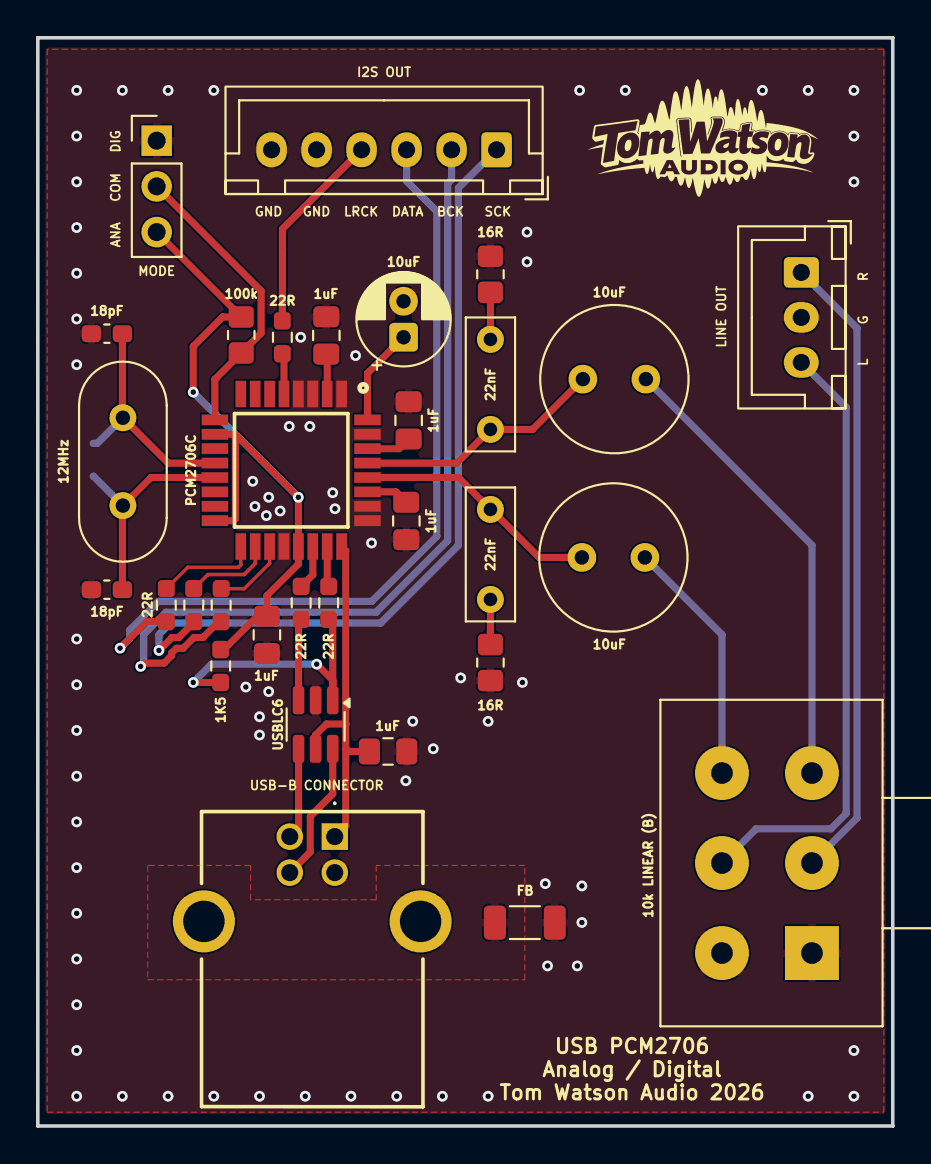
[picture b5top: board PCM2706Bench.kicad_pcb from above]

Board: 2 copper layers, 47.5 x 60.5 mm, 32 parts (1 on the bottom side), 33 nets.

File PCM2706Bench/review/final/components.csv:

Reference,Value,Footprint
C1,10uF,Capacitor_THT:CP_Radial_D5.0mm_P2.00mm
C3,18pF,Capacitor_SMD:C_0603_1608Metric_Pad1.08x0.95mm_HandSolder
C4,18pF,Capacitor_SMD:C_0603_1608Metric_Pad1.08x0.95mm_HandSolder
C11,1uF,Capacitor_SMD:C_1206_3216Metric_Pad1.33x1.80mm_HandSolder
C12,1uF,Capacitor_SMD:C_1206_3216Metric_Pad1.33x1.80mm_HandSolder
C13,1uF,Capacitor_SMD:C_1206_3216Metric_Pad1.33x1.80mm_HandSolder
C14,1uF,Capacitor_SMD:C_1206_3216Metric_Pad1.33x1.80mm_HandSolder
C15,22nF,Capacitor_THT:C_Rect_L7.2mm_W2.5mm_P5.00mm
C16,1uF,Capacitor_SMD:C_1206_3216Metric_Pad1.33x1.80mm_HandSolder
C17,22nF,Capacitor_THT:C_Rect_L7.2mm_W2.5mm_P5.00mm
C21,10uF,Capacitor_THT:C_Radial_D8.0mm_H11.5mm_P3.50mm
C22,10uF,Capacitor_THT:C_Radial_D8.0mm_H11.5mm_P3.50mm
FB1,FB,Inductor_SMD:L_1206_3216Metric_Pad1.22x1.90mm_HandSolder
IC1,PCM2706C,Custom:PCM2706C
IC2,USBLC6,Package_TO_SOT_SMD:SOT-23-6_Handsoldering
J1,MODE,Connector_PinHeader_2.54mm:PinHeader_1x03_P2.54mm_Vertical
J3,USB-B CONNECTOR,Custom:USBC
J4,LINE OUT,Connector_JST:JST_XH_B3B-XH-A_1x03_P2.50mm_Vertical
J5,I2S OUT,Connector_JST:JST_XH_B6B-XH-A_1x06_P2.50mm_Vertical
R2,16R,Resistor_SMD:R_0805_2012Metric_Pad1.20x1.40mm_HandSolder
R3,16R,Resistor_SMD:R_0805_2012Metric_Pad1.20x1.40mm_HandSolder
R4,1K5,Resistor_SMD:R_0603_1608Metric_Pad0.98x0.95mm_HandSolder
R10,22R,Resistor_SMD:R_0603_1608Metric_Pad0.98x0.95mm_HandSolder
R11,22R,Resistor_SMD:R_0603_1608Metric_Pad0.98x0.95mm_HandSolder
R12,22R,Resistor_SMD:R_0603_1608Metric_Pad0.98x0.95mm_HandSolder
R13,22R,Resistor_SMD:R_0603_1608Metric_Pad0.98x0.95mm_HandSolder
R14,22R,Resistor_SMD:R_0603_1608Metric_Pad0.98x0.95mm_HandSolder
R15,22R,Resistor_SMD:R_0603_1608Metric_Pad0.98x0.95mm_HandSolder
R16,1M,Resistor_SMD:R_0603_1608Metric_Pad0.98x0.95mm_HandSolder
R17,100k,Resistor_SMD:R_0805_2012Metric_Pad1.20x1.40mm_HandSolder
RV1,10k LINEAR (B),Potentiometer_THT:Potentiometer_Alps_RK163_Dual_Horizontal
Y1,12MHz,Crystal:Crystal_HC49-U_Vertical
